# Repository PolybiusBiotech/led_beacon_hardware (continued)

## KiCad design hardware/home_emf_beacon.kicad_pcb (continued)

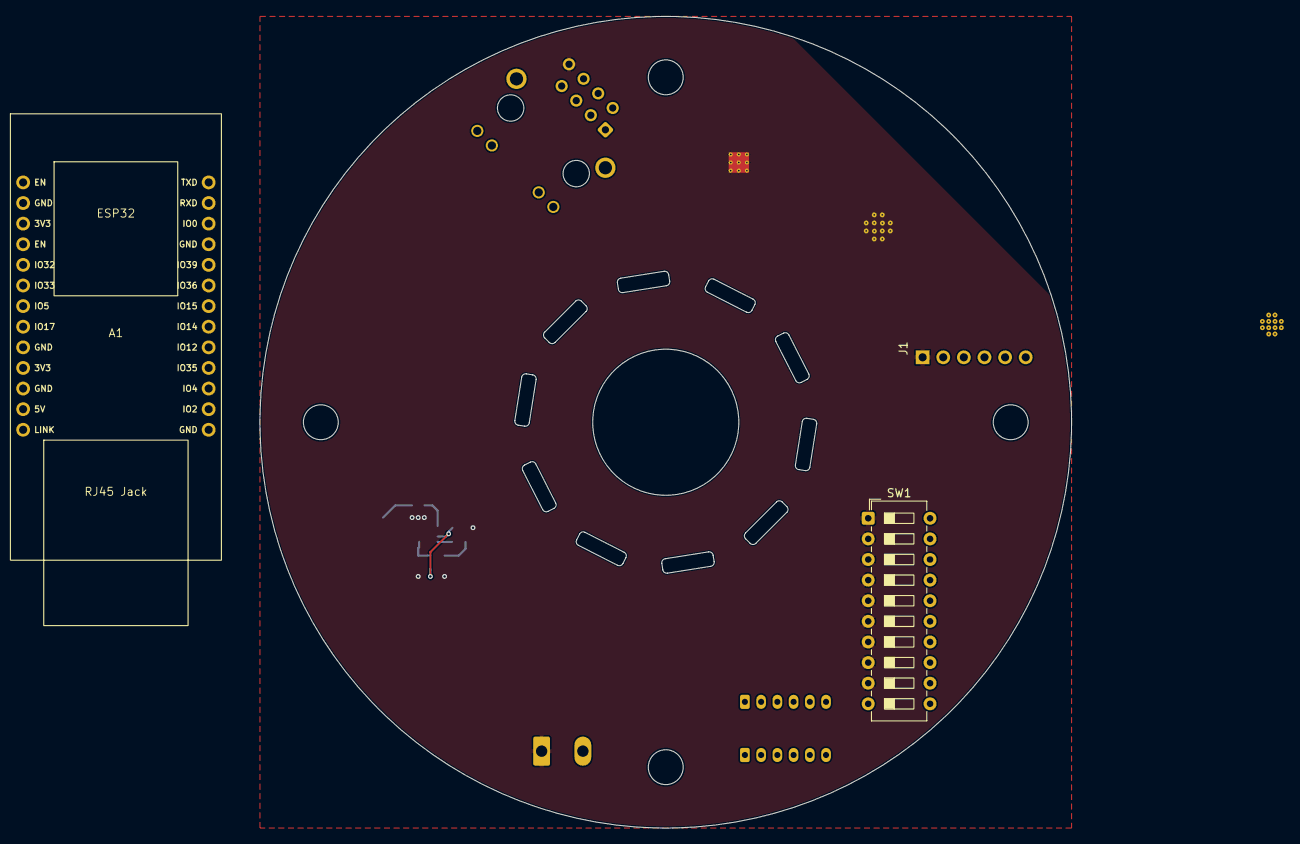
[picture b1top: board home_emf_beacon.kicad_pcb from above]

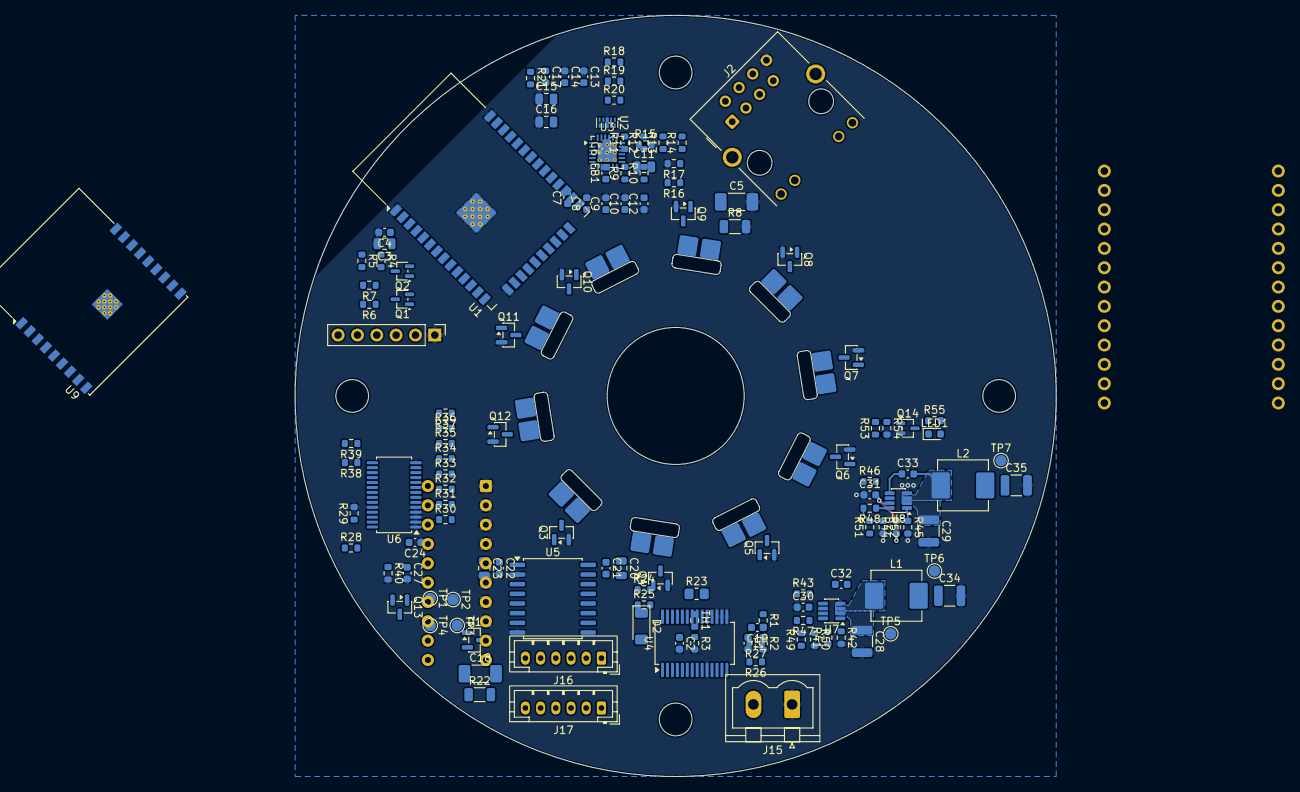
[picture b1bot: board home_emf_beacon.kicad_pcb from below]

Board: 2 copper layers, 100.0 x 100.0 mm, 146 parts (140 on the bottom side), 109 nets.

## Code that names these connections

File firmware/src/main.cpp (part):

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const int wifi_channel = 1;

/** Pin Map **/
#define PIN_TEMP_MON  (0)
#define PIN_VCC_MON   (1)
#define PIN_SDA       (2)
#define PIN_SCL       (3)
#define PIN_I2C_INT   (4)
#define PIN_WIFI_EN   (5)
#define PIN_DMX_EN    (6)
#define PIN_LED_OE    (7)
#define PIN_LED       (8)
//#define PIN_DMX_RX   (20)
//#define PIN_DMX_TX   (21)
// ESP32-C3-DEVKITM-1 uses a USB↔Serial converter attached to IO20/21 not USB on IO18/19!
#define PIN_DMX_RX   (19)
#define PIN_DMX_TX   (18)

/** Hardware instantiations  **/
Adafruit_PWMServoDriver leds = Adafruit_PWMServoDriver(0x40);
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  Serial.write(init_string);

  // init GPIO
  pinMode(PIN_I2C_INT, INPUT);
  pinMode(PIN_LED_OE, OUTPUT);
  pinMode(PIN_DMX_EN, OUTPUT);
  pinMode(PIN_WIFI_EN, INPUT_PULLUP);
  pinMode(PIN_LED, OUTPUT);
  digitalWrite(PIN_LED_OE, HIGH);
  digitalWrite(PIN_DMX_EN, LOW);
  digitalWrite(PIN_LED, LOW);
  analogSetAttenuation(ADC_11db);
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  leds.setPWMFreq(1000);
  leds.setOutputMode(true); // LEDs driven by external NMOS
  for (int i = 0; i < led_count; i++) leds.setPWM(i, 410*i, 0);
  digitalWrite(PIN_LED_OE, LOW); // enable LEDs!
  Serial.println("PCA9685 initialised...");

  // init DMX
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  };
  int personality_count = 1;
  dmx_driver_install(dmx_num, &config, personalities, personality_count);
  dmx_set_pin(dmx_num, PIN_DMX_TX, PIN_DMX_RX, PIN_DMX_EN);
  Serial.println("DMX initialised...");
  
  // init Watchdog
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
    // dealing with excessive temp
    if (current_temp >= warning_temp) {
      digitalWrite(PIN_LED_OE, HIGH); // disable LEDs while too hot!
    } else if (current_temp <= (warning_temp - 5000)) {
      digitalWrite(PIN_LED_OE, LOW); // enable LEDs now it's cooler!
    }
    
    // not sure what actions to take on:      
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    current_uptime = esp_timer_get_time() / 1000000;
       
    // check DMX address
    if (digitalRead(PIN_I2C_INT) == LOW) {
      uint16_t dmx_adr_switches = ~mcp.readGPIOAB(); // read and flip switch states from ACTIVE_LOW to ACTIVE_HIGH
      dmx_adr_switches = (dmx_adr_switches & 0x7F) | ((dmx_adr_switches & 0x0300) >> 1);  // keep 0→6 & 8→9 and concatenate to remove 7
      dmx_address = dmx_adr_switches + 1; // offset and save DMX address
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  int32_t raw_temp = 0x00;

  for (int i = 0; i < 8; i++) {
    raw_temp += analogRead(PIN_TEMP_MON);
    delay(1);
  }
  raw_temp /= 8;
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
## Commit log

2026-04-20 adjusting folders
2026-04-20 removing old board files
2026-04-21 tweaking workflow
2026-04-21 more tweaking
2026-04-21 docs: auto-generate schematic PDF
2026-04-21 fixing issues, adding parts
2026-04-24 Update MCP23017
2026-04-25 adding uptime
2026-04-26 Improving serial statuses
2026-04-27 small tweaks
2026-04-27 Update main.cpp
    Adding period mapping
2026-04-27 Update main.cpp
    Adding DMX timeout functionality
2026-04-27 Update main.cpp
    Fixing strobe data offset.
2026-04-27 Update main.cpp
    Trying to add a way to disable the WiFi AP
2026-04-27 Update main.cpp
    Adding webpage stats
2026-04-27 Update main.cpp
    Adding better status page
2026-04-27 fixed web status
2026-04-27 fixed timer
2026-05-01 tweaking README.md formatting
